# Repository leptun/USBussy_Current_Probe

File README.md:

# USBussy_Current_Probe

This project is a simple USB current probe for my PC. It can function in two modes which are selctable via jumpers:
- As two ganged USB downstream facing ports (1x typeA, 1x typeC) that are connected to my PC's internal USB 2.0 headers.
- As a single typeA downstream facing port with a typeC upstream facing port.

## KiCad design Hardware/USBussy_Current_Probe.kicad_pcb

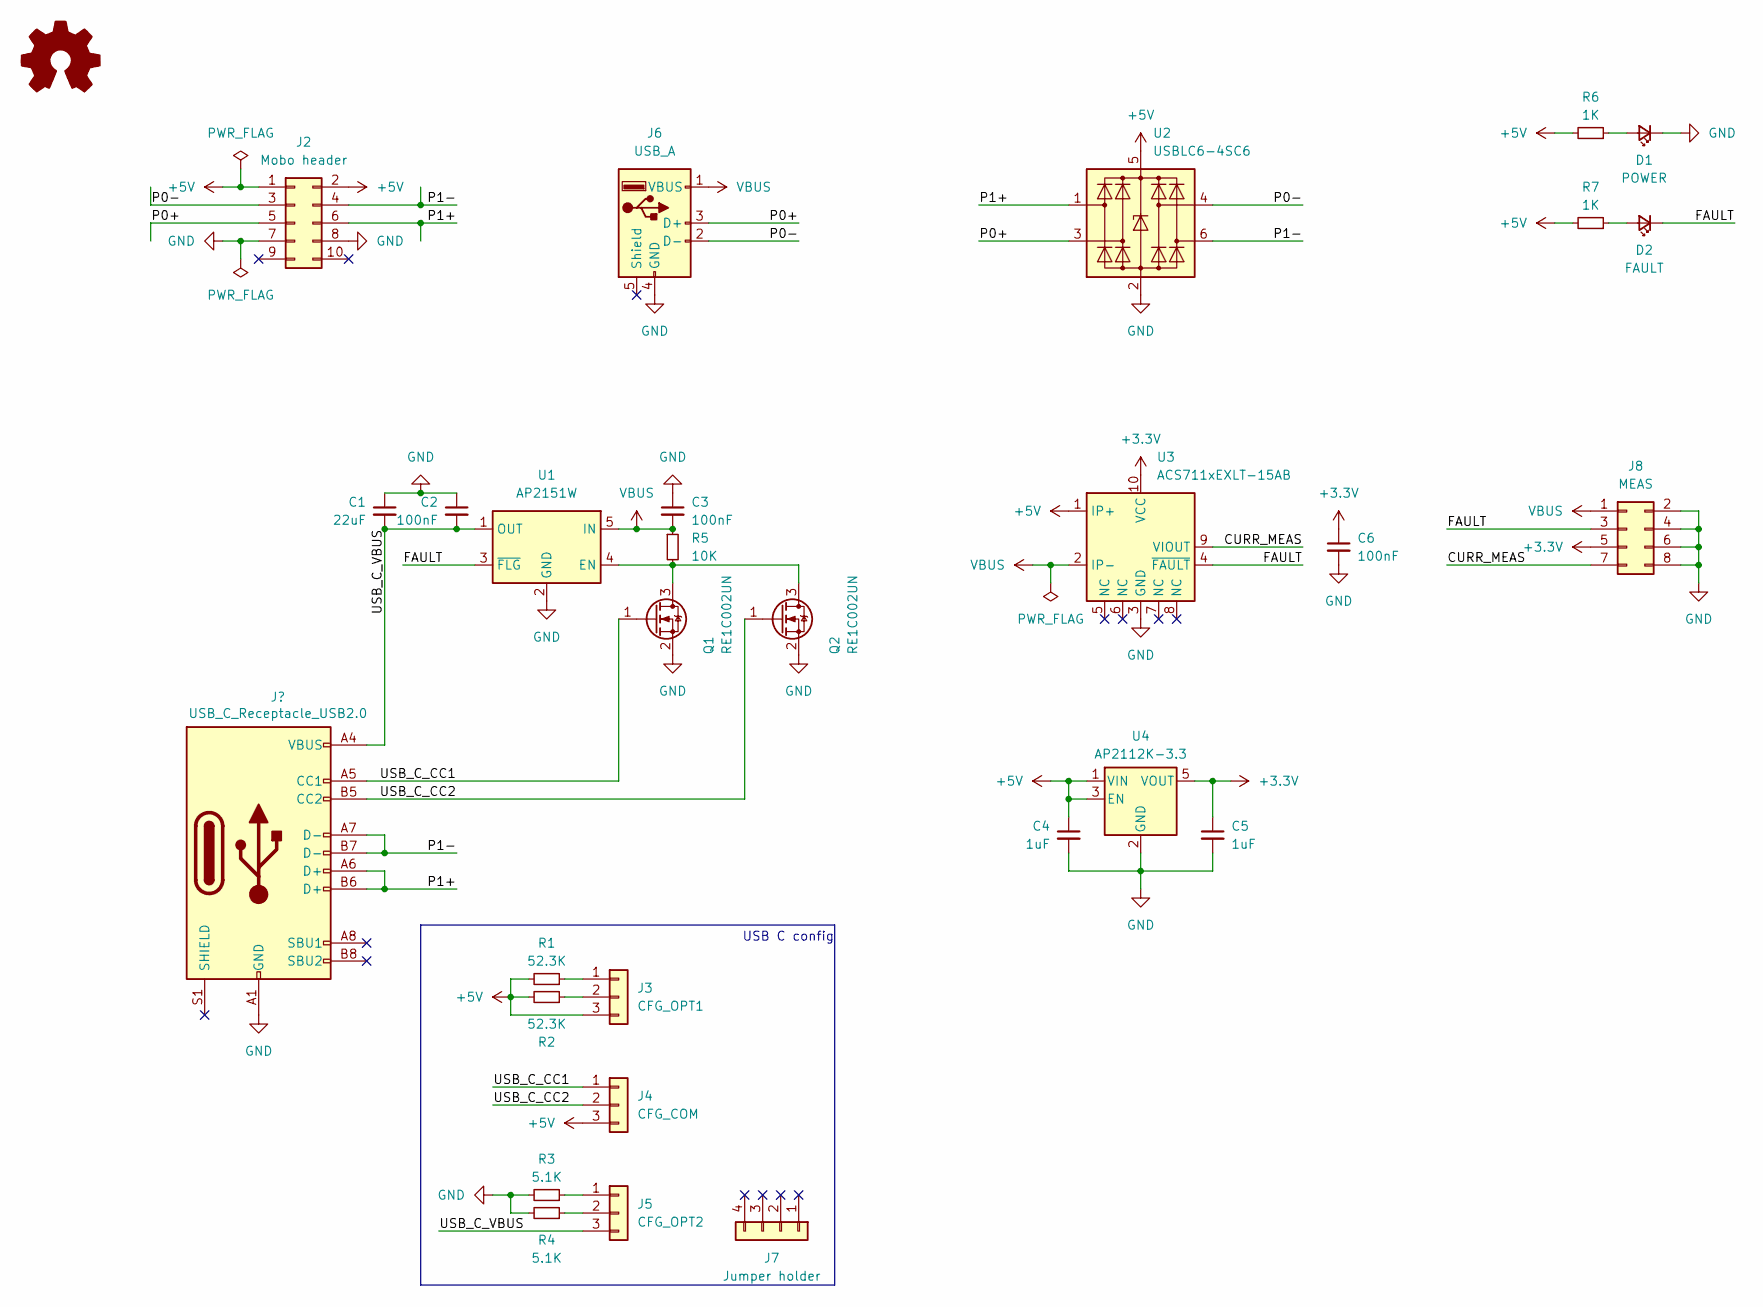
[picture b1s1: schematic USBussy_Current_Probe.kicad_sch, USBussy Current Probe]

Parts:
C1: 22uF; C_1210_3225Metric
C2, C3, C6: 100nF; C_0603_1608Metric
C4, C5: 1uF; C_0805_2012Metric
D1: POWER; LED_1206_3216Metric
D2: FAULT; LED_1206_3216Metric
J1: USB_C_Receptacle_USB2.0; USB4110-GF-A
J2: Mobo header; PinHeader_2x05_P2.54mm_Vertical
J3: CFG_OPT1; PinHeader_1x03_P2.54mm_Vertical
J4: CFG_COM; PinHeader_1x03_P2.54mm_Vertical
J5: CFG_OPT2; PinHeader_1x03_P2.54mm_Vertical
J6: USB_A; 67643-0910
J7: Jumper holder; PinHeader_1x04_P2.54mm_Vertical
J8: MEAS; PinHeader_2x04_P2.54mm_Vertical
Q1, Q2: RE1C002UN; SOT-416
R1, R2: 52.3K; R_0603_1608Metric
R3, R4: 5.1K; R_0603_1608Metric
R5: 10K; R_0603_1608Metric
R6, R7: 1K; R_0805_2012Metric
SYM1: AMOGUS
U1: AP2151W; SOT-23-5
U2: USBLC6-4SC6; SOT-23-6
U3: ACS711xEXLT-15AB; Allegro_QFN-12-10-1EP_3x3mm_P0.5mm
U4: AP2112K-3.3; SOT-23-5

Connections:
+3.3V: C5.1, C6.1, J8.5, U3.10 (VCC), U4.5 (VOUT)
+5V: C4.1, J2.1, J2.2, J3.3, J4.3, R1.2, R2.2, R6.2, R7.2, U2.5 (VBUS), U3.1 (IP+), U4.1 (VIN), U4.3 (EN)
/CURR_MEAS: J8.7, U3.9 (VIOUT)
/FAULT: D2.1 (K), J8.3, U1.3 (~FLG), U3.4 (~FAULT)
/P0+: J2.5, J6.3 (D+), U2.3 (I/O2)
/P0-: J2.3, J6.2 (D-), U2.4 (I/O3)
/P1+: J1.A6 (D+), J1.B6 (D+), J2.6, U2.1 (I/O1)
/P1-: J1.A7 (D-), J1.B7 (D-), J2.4, U2.6 (I/O4)
/USB_C_CC1: J1.A5 (CC1), J4.1, Q1.1 (G)
/USB_C_CC2: J1.B5 (CC2), J4.2, Q2.1 (G)
/USB_C_VBUS: C1.2, C2.2, J1.A4 (VBUS), J1.A9 (VBUS), J1.B4 (VBUS), J1.B9 (VBUS), J5.3, U1.1 (OUT)
GND: C1.1, C2.1, C3.1, C4.2, C5.2, C6.2, D1.1 (K), J1.A1 (GND), J1.A12 (GND), J1.B1 (GND), J1.B12 (GND), J2.7, J2.8, J6.4 (GND), J8.2, J8.4, J8.6, J8.8, Q1.2 (S), Q2.2 (S), R3.2, R4.2, U1.2 (GND), U2.2 (GND), U3.3 (GND), U4.2 (GND)
unnamed: D1.2 (A), R6.1
unnamed: D2.2 (A), R7.1
unnamed: J3.1, R1.1
unnamed: J3.2, R2.1
unnamed: J5.1, R3.1
unnamed: J5.2, R4.1
unnamed: Q1.3 (D), Q2.3 (D), R5.2, U1.4 (EN)
VBUS: C3.2, J6.1 (VBUS), J8.1, R5.1, U1.5 (IN), U3.2 (IP-)

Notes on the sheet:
USB C config

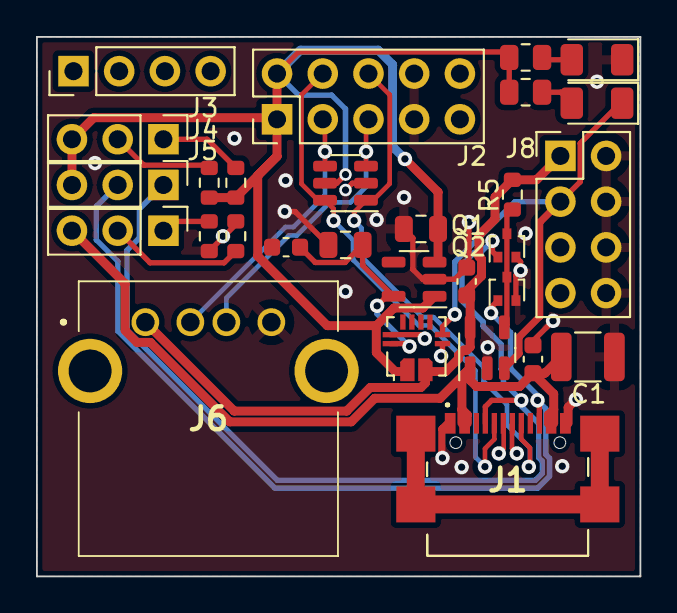
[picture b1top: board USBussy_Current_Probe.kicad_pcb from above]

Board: 4 copper layers, 33.5 x 30.0 mm, 30 parts (1 on the bottom side), 20 nets.

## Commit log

2024-02-15 Add texts on board and export
2024-02-16 Add pinout on silkscreen
2024-02-18 Add readme and pictures
